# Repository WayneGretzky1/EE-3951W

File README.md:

# Strain guage

You will be designing and building a weight scale using a pre-built strain gauge bridge as shown in the link below:

Note that this package comes with a circuit board containing a custom load cell amplifier and 24 bit analog to digital converter (ADC). You will NOT be allowed to use this for your project. Instead, you will be reading the strain gauge output with the 10-bit ADC available on the Microchip PIC24FJ64GA002 microcontroller and the weight displayed on an appropriate LCD display. 

_**Detailed Specifications:**_

The system should display the weight of a test weight, in grams, to the nearest gram. The range should be 0-1000 grams. The system should have an auto zero ("tare") button to correct for any offset error. Note that a 10-bit ADC only has 1024 quantization levels so the system cannot correct large offset errors by digital offsets. Power supplies may be batteries, USB power, or wall power - it's your choice. The final system should function independently (not be tethered to a laptop other than possibly for power). More details will be provided in class.

_**The Boring Stuff:**_

1. Since the analog portion of the circuit will be connected to the analog to digital converter on your PIC board, putting the analog circuit in a box is not necessary, but you should plan on having it mounted in a stable fashion to facilitate testing and demonstration, If you do choose to put the circuit in a box, we suggest the  Bud 750-1015 box or equivalent, available from the ECE Depot, but other creative solutions are fine too including 3D printed boxes (there seems to be a competition every semester for who can make the cutest box); that's fine, but don't obsess too much about the box. The whole thing should be reasonable sized (6” on a side or less), if you feel you need to make a bigger board/box, please consult your TA first.

2. Components should be available from Digi-Key (they have the quickest delivery), Mouser Electronics (they are not quite as quick to ship as Digi-Key), or standard items from the ECE Depot. These parts will be ordered through the ECE Depot. A single IC containing the entire project is not permitted. If you wish to incorporate other parts from other suppliers you will be responsible for ordering and paying for them – we will not reimburse groups for these out of pocket expenses.

3. Instructions for Ordering Parts From the ECE Depot  Download Instructions for Ordering Parts From the ECE Depot(These instructions are from Fall 2023 but are still correct).

NOTE: not all parts listed in the supplier catalog are in stock, and ordering out of stock parts may result in substantial delays. Many parts are also surface mount – surface mount parts are often quite small and difficult to solder – if leaded parts (packages with leads like the ones you can plug into a proto-board) are available, they are usually the best choice. We have soldering facilities available in Anderson Labs, the ECE Depot (during the hours the Depot is open), and in the EXCEED lab.

Please designate ONE PERSON form your group to do all of the interfacing with the ECE Depot.

4. The total cost of all parts ordered through the ECE depot should not exceed $50. The circuit board, thermocouple wire, and thermocouple connectors do not need to be included in your budget.

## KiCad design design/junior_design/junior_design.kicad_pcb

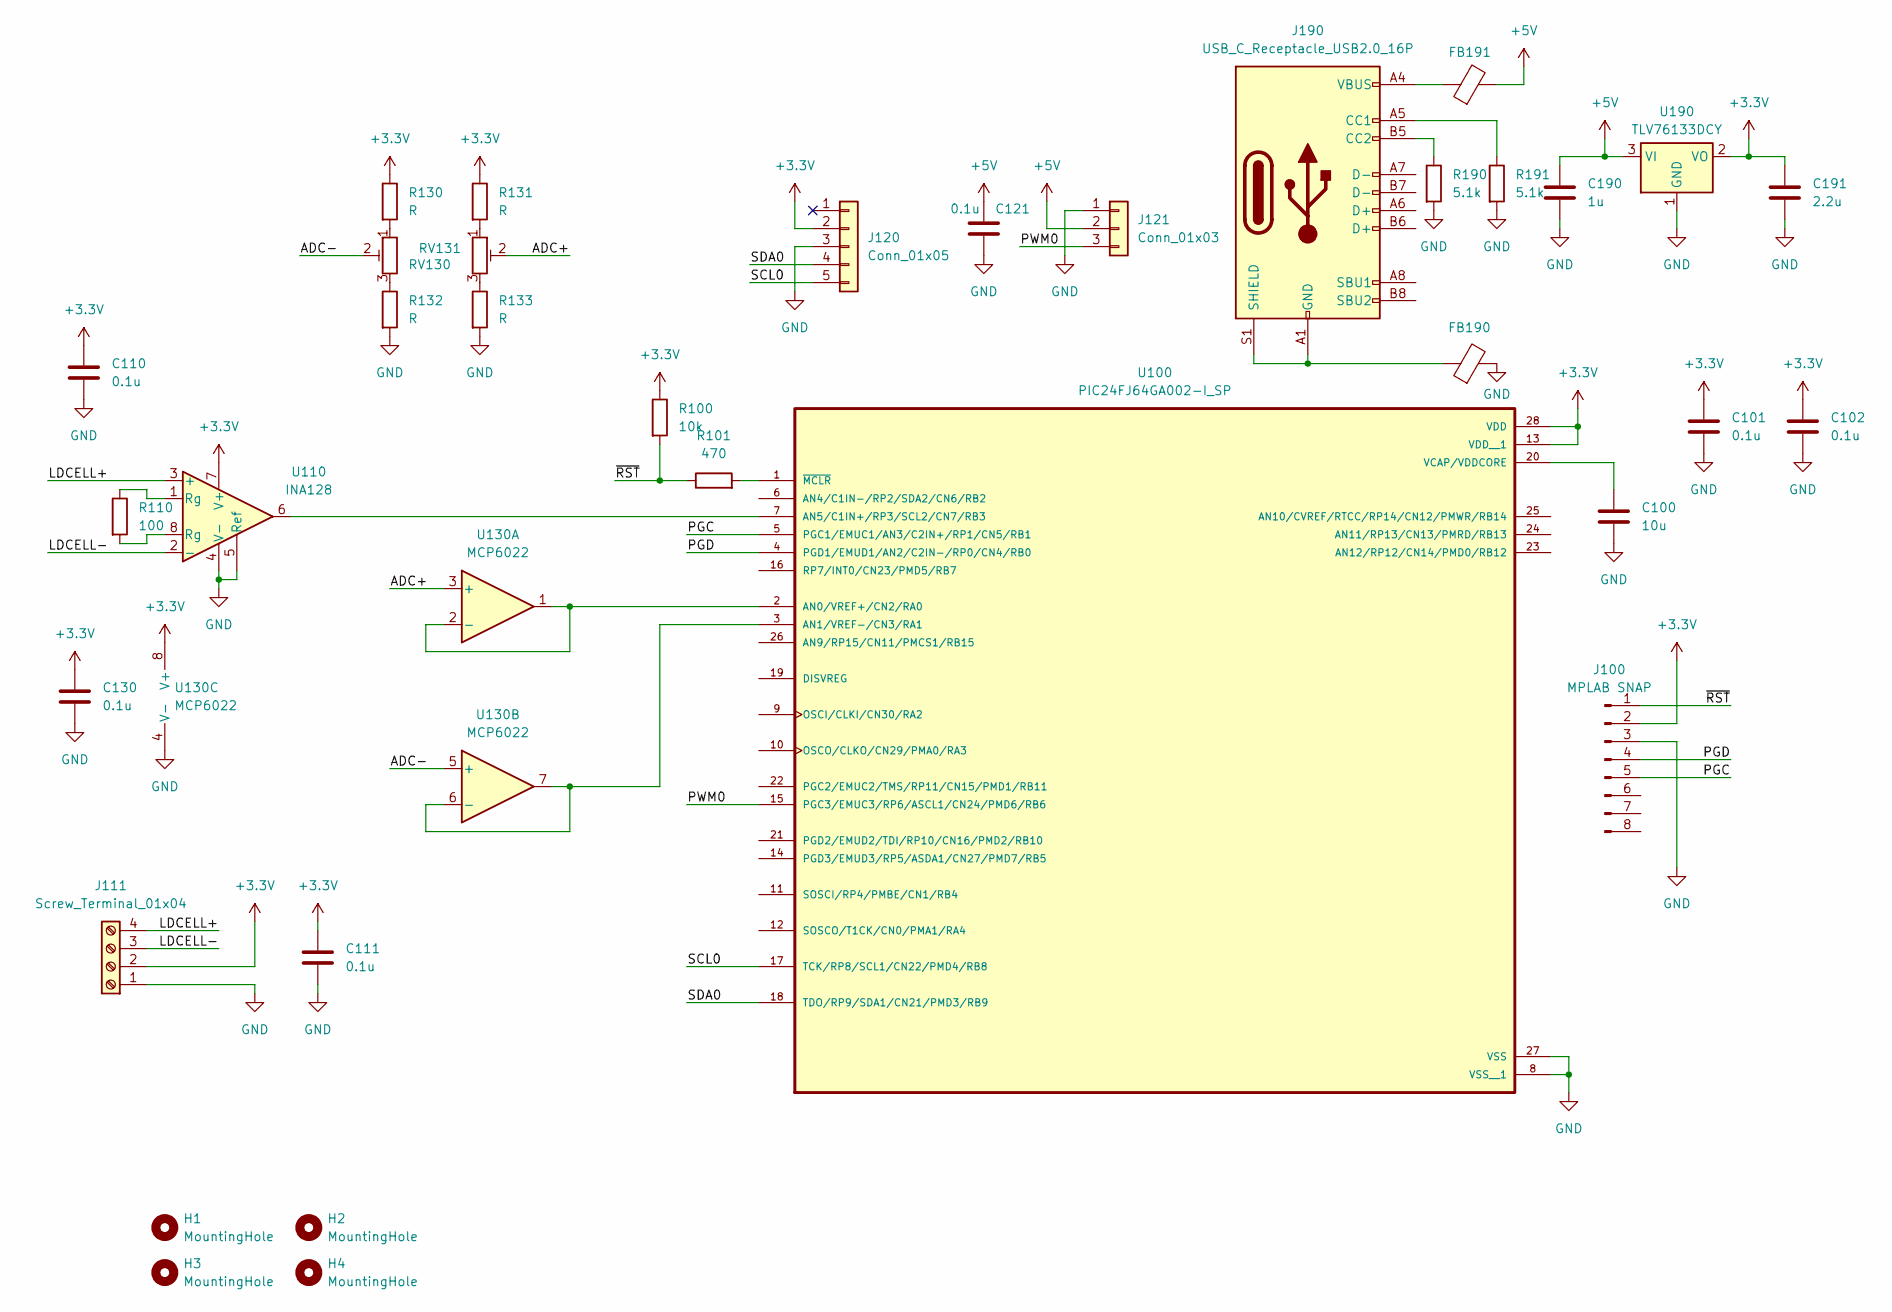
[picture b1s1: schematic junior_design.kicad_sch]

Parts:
C100: 10u; C_0805_2012Metric_Pad1.18x1.45mm_HandSolder
C101, C102, C110, C111, C121, C130: 0.1u; C_0603_1608Metric_Pad1.08x0.95mm_HandSolder
C190: 1u; C_0603_1608Metric_Pad1.08x0.95mm_HandSolder
C191: 2.2u; C_0603_1608Metric_Pad1.08x0.95mm_HandSolder
FB190, FB191: FerriteBead; L_0603_1608Metric_Pad1.05x0.95mm_HandSolder
H1, H2, H3, H4: MountingHole; MountingHole_2.7mm
J100: MPLAB SNAP; PinHeader_1x08_P2.54mm_Horizontal
J111: Screw_Terminal_01x04; PhoenixContact_MC_1,5_4-G-3.81_1x04_P3.81mm_Horizontal
J120: Conn_01x05; PinHeader_1x05_P2.54mm_Vertical
J121: Conn_01x03; PinHeader_1x03_P2.54mm_Vertical
J190: USB_C_Receptacle_USB2.0_16P; USB_C_Receptacle_GCT_USB4085
R100: 10k; R_0603_1608Metric_Pad0.98x0.95mm_HandSolder
R101: 470; R_0603_1608Metric_Pad0.98x0.95mm_HandSolder
R110: 100; R_0603_1608Metric_Pad0.98x0.95mm_HandSolder
R130, R131, R132, R133: R; R_0603_1608Metric_Pad0.98x0.95mm_HandSolder
R190, R191: 5.1k; R_0603_1608Metric_Pad0.98x0.95mm_HandSolder
RV130, RV131: R_Potentiometer_Trim; Potentiometer_Bourns_3266Y_Vertical
U100: PIC24FJ64GA002-I_SP; DIP-28_W7.62mm
U110: INA128; DIP-8_W7.62mm
U130: MCP6022; DIP-8_W7.62mm
U190: TLV76133DCY; SOT-223-3_TabPin2

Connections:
+3.3V: C101.1, C102.1, C110.1, C111.1, C130.1, C191.1, J100.2, J111.2, J120.2, R100.1, R130.1, R131.1, U100.13 (VDD__1), U100.28 (VDD), U110.7 (V+), U130.8 (V+), U190.2 (VO)
+5V: C121.1, C190.1, FB191.2, J121.2, U190.3 (VI)
/ADC+: RV131.2, U130.3 (+)
/ADC-: RV130.2, U130.5 (+)
/LDCELL+: J111.4, U110.3 (+)
/LDCELL-: J111.3, U110.2 (-)
/PGC: J100.5, U100.5 (PGC1/EMUC1/AN3/C2IN+/RP1/CN5/RB1)
/PGD: J100.4, U100.4 (PGD1/EMUD1/AN2/C2IN-/RP0/CN4/RB0)
/PWM0: J121.3, U100.15 (PGC3/EMUC3/RP6/ASCL1/CN24/PMD6/RB6)
/SCL0: J120.5, U100.17 (TCK/RP8/SCL1/CN22/PMD4/RB8)
/SDA0: J120.4, U100.18 (TDO/RP9/SDA1/CN21/PMD3/RB9)
/~RST: J100.1, R100.2, R101.1
GND: C100.2, C101.2, C102.2, C110.2, C111.2, C121.2, C130.2, C190.2, C191.2, FB190.2, J100.3, J111.1, J120.3, J121.1, R132.2, R133.2, R190.2, R191.2, U100.8 (VSS__1), U100.27 (VSS), U110.4 (V-), U110.5 (Ref), U130.4 (V-), U190.1 (GND)
unnamed: FB191.1, J190.A4 (VBUS), J190.A9 (VBUS), J190.B4 (VBUS), J190.B9 (VBUS)
unnamed: J190.A5 (CC1), R191.1
unnamed: J190.B5 (CC2), R190.1
unnamed: FB190.1, J190.A1 (GND), J190.A12 (GND), J190.B1 (GND), J190.B12 (GND), J190.S1 (SHIELD)
unnamed: R110.1, U110.1 (Rg)
unnamed: R110.2, U110.8 (Rg)
unnamed: R130.2, RV130.1
unnamed: R131.2, RV131.1
unnamed: R132.1, RV130.3
unnamed: R133.1, RV131.3
unnamed: U100.2 (AN0/VREF+/CN2/RA0), U130.1, U130.2 (-)
unnamed: U100.3 (AN1/VREF-/CN3/RA1), U130.6 (-), U130.7
unnamed: U100.7 (AN5/C1IN+/RP3/SCL2/CN7/RB3), U110.6
unnamed: C100.1, U100.20 (VCAP/VDDCORE)
unnamed: R101.2, U100.1 (~MCLR)

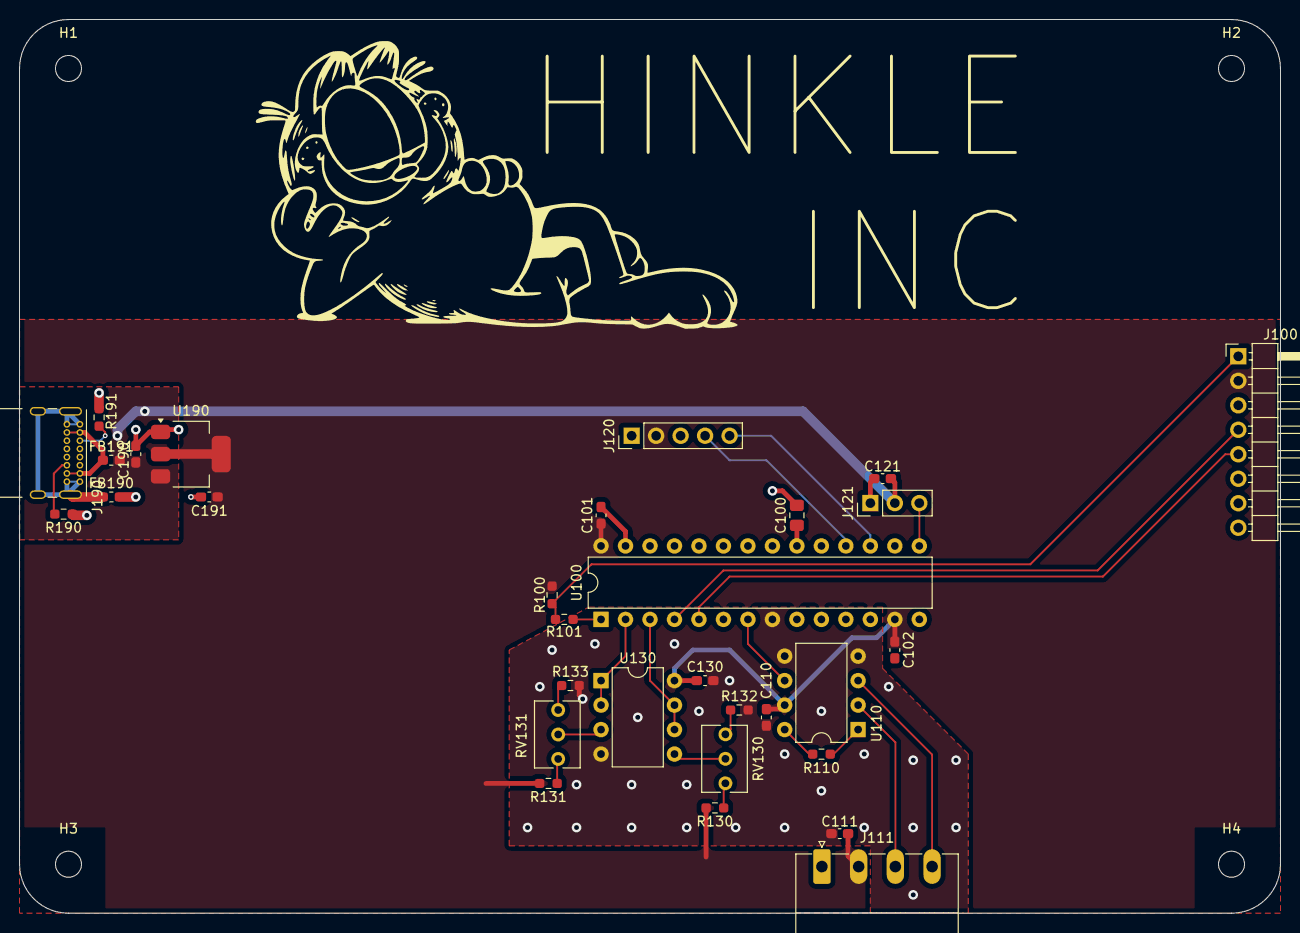
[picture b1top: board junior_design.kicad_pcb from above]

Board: 2 copper layers, 130.8 x 92.7 mm, 35 parts (0 on the bottom side), 28 nets.

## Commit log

2024-09-10 "update folder"
2024-09-10 "Update folder name"
2024-09-10 Create empty
2024-09-17 "add design folder"
2024-09-17 Added MPLAB project
2024-09-17 Added simple main and adc lib files to project
2024-09-24 added working pin select and reference voltages
2024-10-01 Added LCD lib to project
2024-10-08 Added LCD display code and ADC is working
2024-10-08 Changed bufferLib
2024-10-15 add kicad design to repo
2024-10-15 changed .gitignore
2024-10-15 add pcb
2024-10-15 Started PCB layout
2024-10-15 Finish routing PCB
2024-10-17 add ferrite beads to usb-c port
2024-11-05 Got the ADC working
2024-11-20 Add servo files
2024-11-26 Changed Analog input port
2024-12-03 Fixed ADC, and added working servo code
2024-12-10 Final changes before the presentation
